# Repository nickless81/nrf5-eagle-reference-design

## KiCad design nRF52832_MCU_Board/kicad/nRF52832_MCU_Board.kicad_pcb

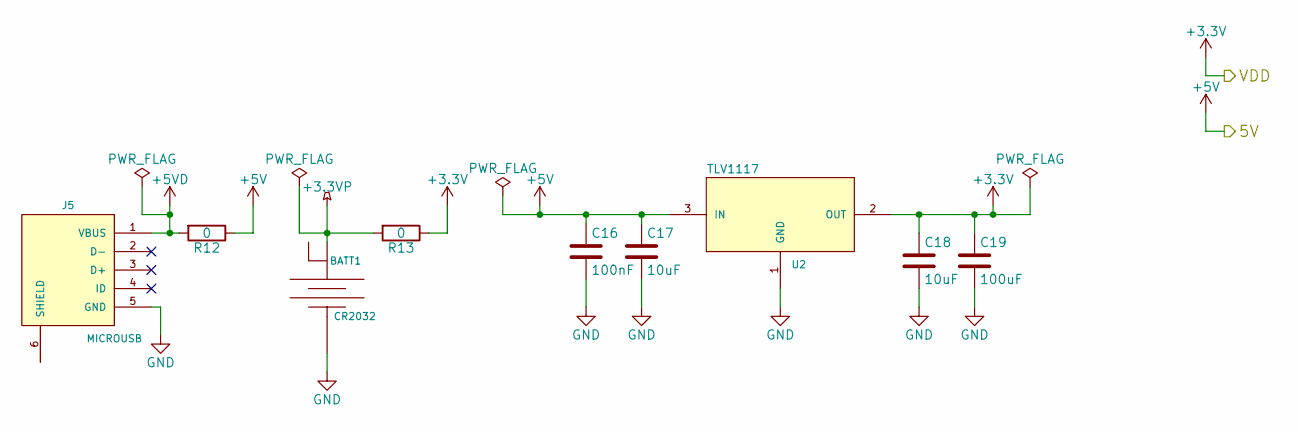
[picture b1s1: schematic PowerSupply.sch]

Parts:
BATT1: CR2032; keystone_3003
C16: 100nF; C_0402
C17, C18: 10uF; C_0603
C19: 100uF; C_0805
J5: MICROUSB; conn_usb_B_micro_smd
R12, R13: 0; R_0402
U2: TLV1117; SOT-223-3Lead_TabPin2

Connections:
+3.3VP: BATT1.2 (+), R13.2
+3V3: C18.1, C19.1, R13.1, U2.2 (OUT); also elsewhere on the board
+5V: C16.1, C17.1, R12.1, U2.3 (IN); also elsewhere on the board
+5VD: J5.1 (VBUS), R12.2
GND: BATT1.1 (-), C16.2, C17.2, C18.2, C19.2, J5.5 (GND), U2.1 (GND); also elsewhere on the board

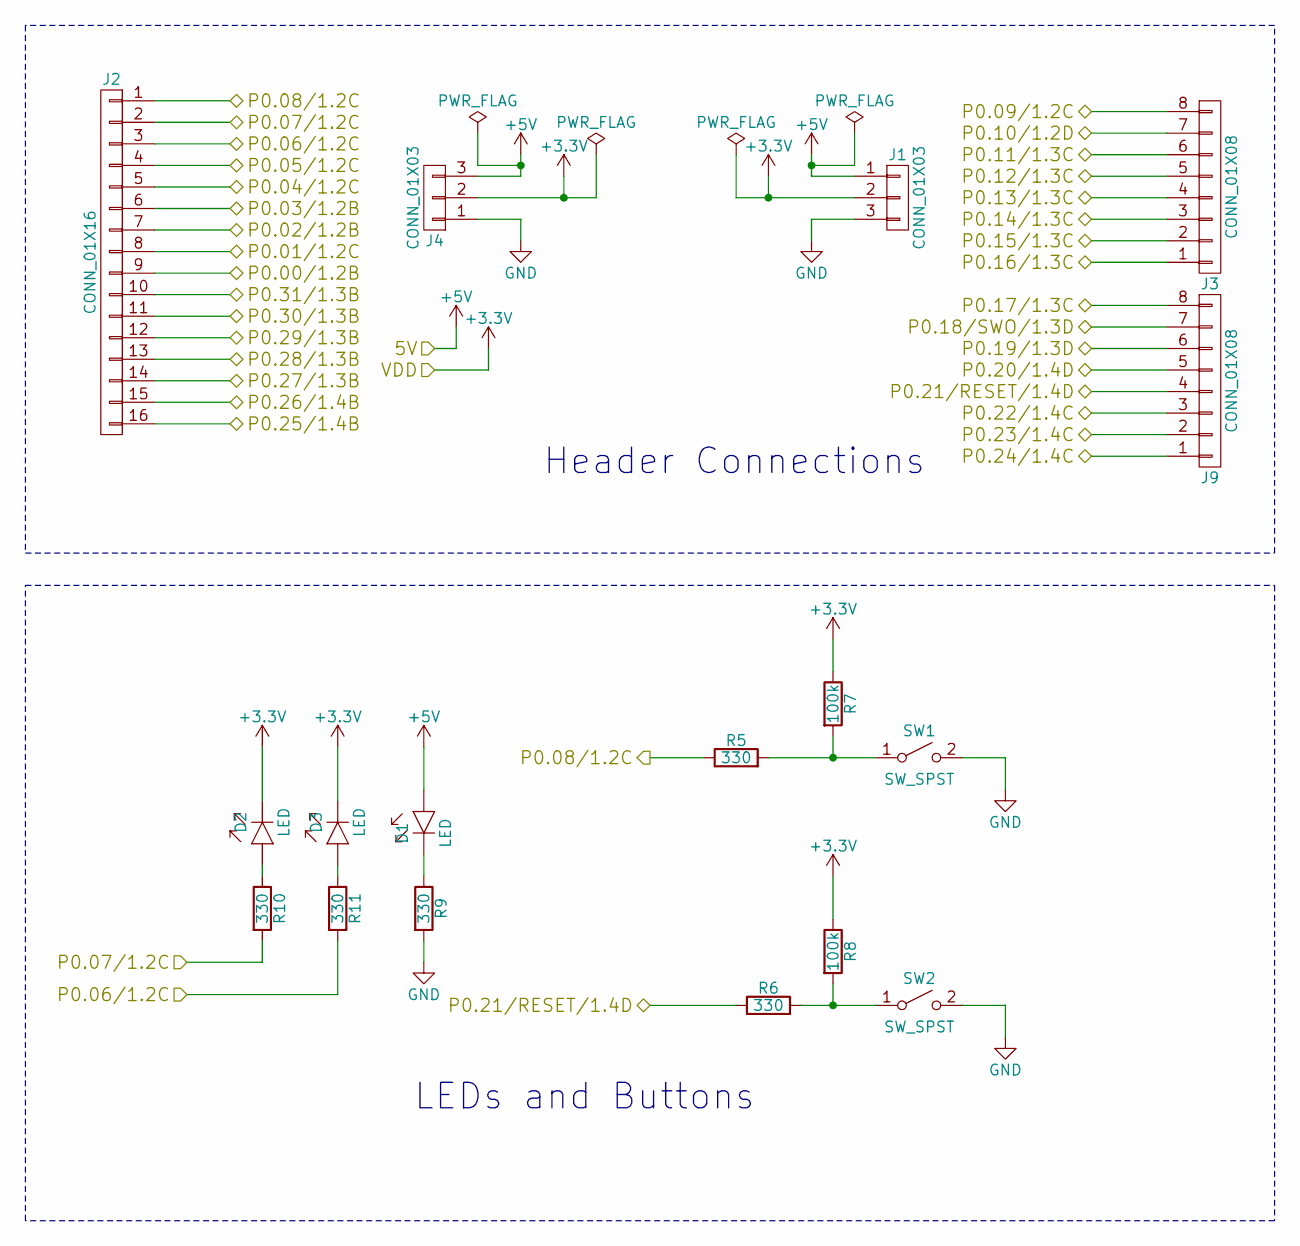
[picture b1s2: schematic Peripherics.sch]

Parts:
D1, D2, D3: LED; LED_0603
J1, J4: CONN_01X03; Pin_Header_Straight_1x03_Pitch2.54mm
J2: CONN_01X16; Pin_Header_Straight_1x16_Pitch2.54mm
J3, J9: CONN_01X08; Pin_Header_Straight_1x08_Pitch2.54mm
R5, R6, R9, R10, R11: 330; R_0402
R7, R8: 100k; R_0402
SW1, SW2: SW_SPST; SW_SPST_FSMSM

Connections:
+3V3: D2.1 (C), D3.1 (C), J1.2, J4.2, R7.1, R8.1; also elsewhere on the board
+5V: D1.2 (A), J1.1, J4.3; also elsewhere on the board
/P0.00: J2.9; also elsewhere on the board
/P0.01: J2.8; also elsewhere on the board
/P0.02: J2.7; also elsewhere on the board
/P0.03: J2.6; also elsewhere on the board
/P0.04: J2.5; also elsewhere on the board
/P0.05: J2.4; also elsewhere on the board
/P0.06: J2.3, R11.2; also elsewhere on the board
/P0.07: J2.2, R10.2; also elsewhere on the board
/P0.08: J2.1, R5.1; also elsewhere on the board
/P0.09: J3.8; also elsewhere on the board
/P0.10: J3.7; also elsewhere on the board
/P0.11: J3.6; also elsewhere on the board
/P0.12: J3.5; also elsewhere on the board
/P0.13: J3.4; also elsewhere on the board
/P0.14: J3.3; also elsewhere on the board
/P0.15: J3.2; also elsewhere on the board
/P0.16: J3.1; also elsewhere on the board
/P0.17: J9.8; also elsewhere on the board
/P0.18: J9.7; also elsewhere on the board
/P0.19: J9.6; also elsewhere on the board
/P0.20: J9.5; also elsewhere on the board
/P0.21: J9.4, R6.1; also elsewhere on the board
/P0.22: J9.3; also elsewhere on the board
/P0.23: J9.2; also elsewhere on the board
/P0.24: J9.1; also elsewhere on the board
/P0.25: J2.16; also elsewhere on the board
/P0.26: J2.15; also elsewhere on the board
/P0.27: J2.14; also elsewhere on the board
/P0.28: J2.13; also elsewhere on the board
/P0.29: J2.12; also elsewhere on the board
/P0.30: J2.11; also elsewhere on the board
/P0.31: J2.10; also elsewhere on the board
GND: J1.3, J4.1, R9.2, SW1.2 (B), SW2.2 (B); also elsewhere on the board
unnamed: D1.1 (C), R9.1
unnamed: D2.2 (A), R10.1
unnamed: D3.2 (A), R11.1
unnamed: R5.2, R7.2, SW1.1 (A)
unnamed: R6.2, R8.2, SW2.1 (A)

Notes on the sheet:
Header Connections
LEDs and Buttons

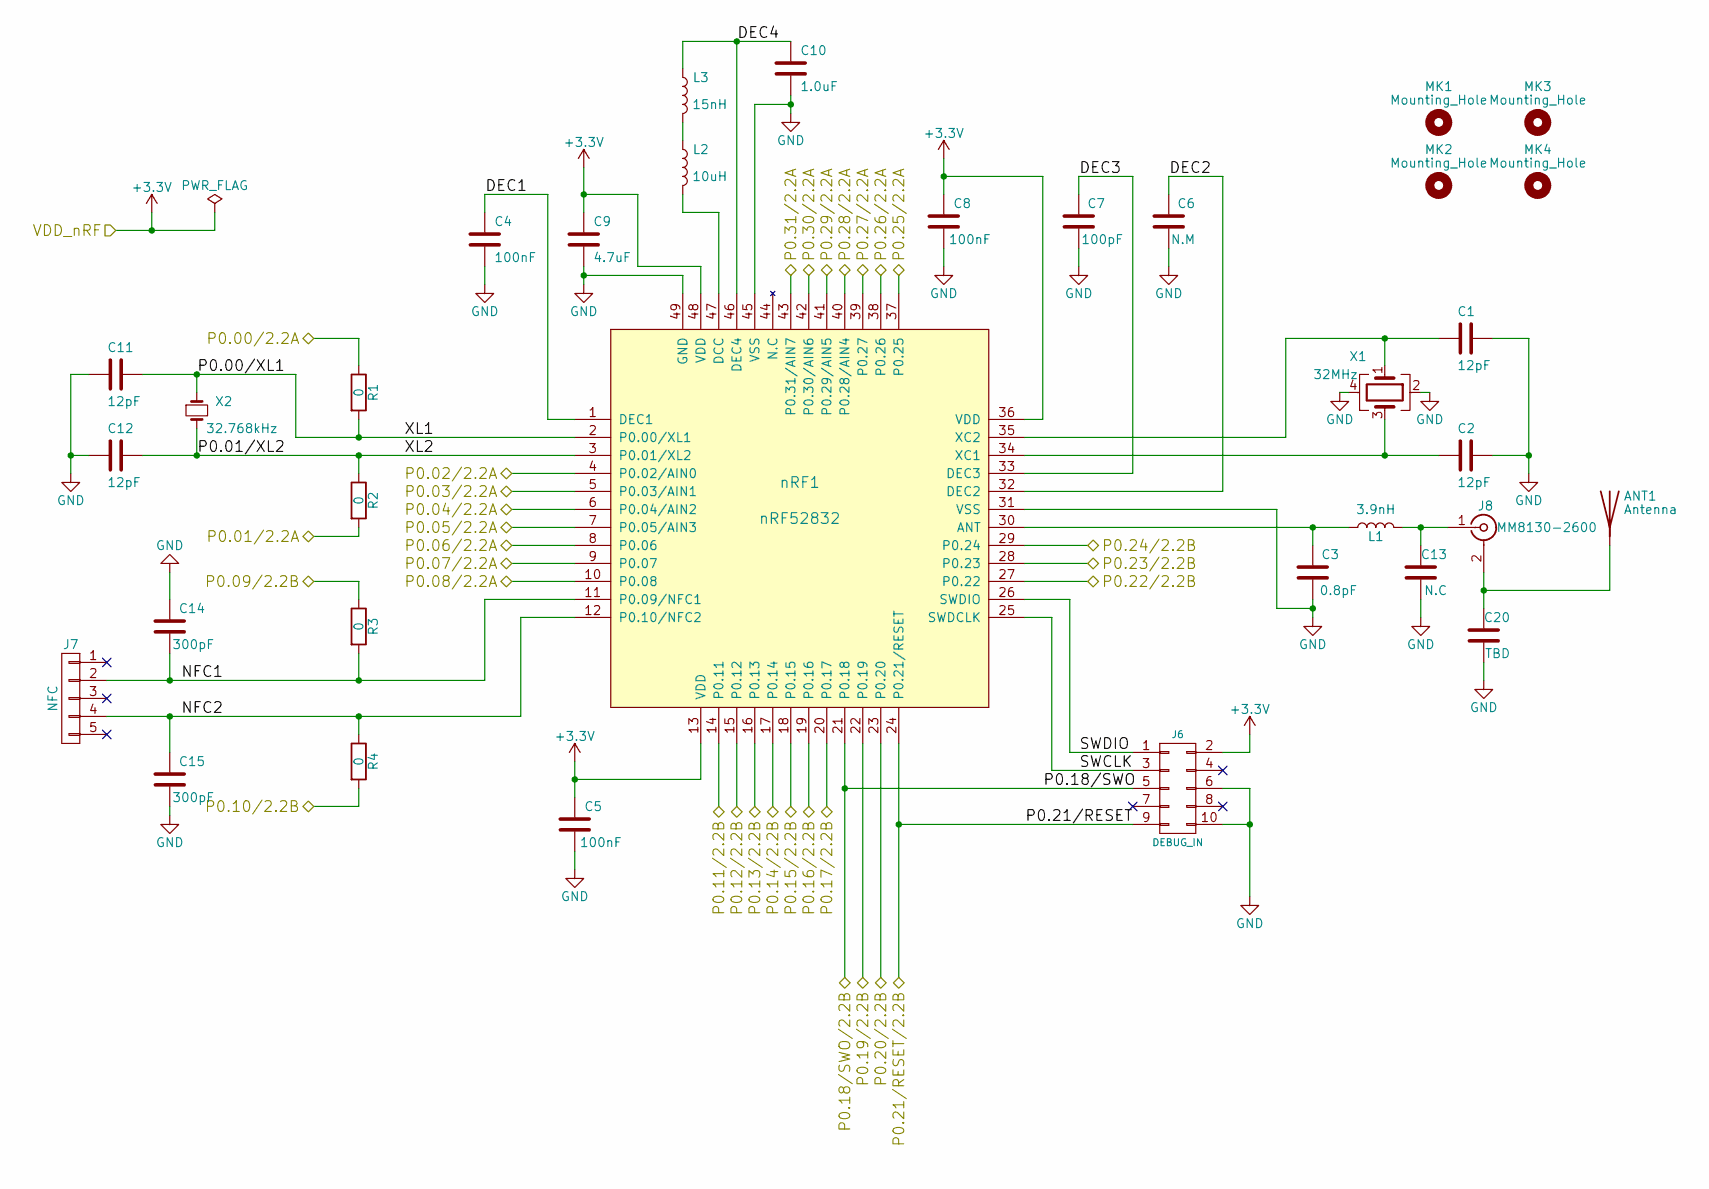
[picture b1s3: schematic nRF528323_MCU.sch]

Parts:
ANT1: Antenna; Nordic_misc-QWMP_MEANDERED_LEFT_+6
C1, C2, C11, C12: 12pF; C_0402
C3: 0.8pF; C_0402
C4, C5, C8: 100nF; C_0402
C6: N.M; C_0402
C7: 100pF; C_0402
C9: 4.7uF; C_0603
C10: 1.0uF; C_0603
C13: N.C; C_0402
C14, C15: 300pF; C_0402
C20: TBD; C_0402
J6: DEBUG_IN; ftsh-105-01-l-dv
J7: NFC; Nordic_misc-FPC_05P-RA-SMD
J8: MM8130-2600; Nordic_misc-MM8130-2600
L1: 3.9nH; L_0402
L2: 10uH; L_0603
L3: 15nH; L_0402
MK1, MK2, MK3, MK4: Mounting_Hole; MountingHole_3mm
R1, R2, R3, R4: 0; R_0402
X1: 32MHz; Crystal_SMD_2016-4pin_2.0x1.6mm
X2: 32.768kHz; Crystal_SMD_3215-2pin_3.2x1.5mm
nRF1: nRF52832; Nordic_nRF-QFN40P600X600X90-48_N

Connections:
+3V3: C5.1, C8.1, C9.1, J6.2, nRF1.13 (VDD), nRF1.36 (VDD), nRF1.48 (VDD); also elsewhere on the board
/P0.00: R1.1; also elsewhere on the board
/P0.01: R2.2; also elsewhere on the board
/P0.02: nRF1.4 (P0.02/AIN0); also elsewhere on the board
/P0.03: nRF1.5 (P0.03/AIN1); also elsewhere on the board
/P0.04: nRF1.6 (P0.04/AIN2); also elsewhere on the board
/P0.05: nRF1.7 (P0.05/AIN3); also elsewhere on the board
/P0.06: nRF1.8 (P0.06); also elsewhere on the board
/P0.07: nRF1.9 (P0.07); also elsewhere on the board
/P0.08: nRF1.10 (P0.08); also elsewhere on the board
/P0.09: R3.1; also elsewhere on the board
/P0.10: R4.2; also elsewhere on the board
/P0.11: nRF1.14 (P0.11); also elsewhere on the board
/P0.12: nRF1.15 (P0.12); also elsewhere on the board
/P0.13: nRF1.16 (P0.13); also elsewhere on the board
/P0.14: nRF1.17 (P0.14); also elsewhere on the board
/P0.15: nRF1.18 (P0.15); also elsewhere on the board
/P0.16: nRF1.19 (P0.16); also elsewhere on the board
/P0.17: nRF1.20 (P0.17); also elsewhere on the board
/P0.18: J6.5, nRF1.21 (P0.18); also elsewhere on the board
/P0.19: nRF1.22 (P0.19); also elsewhere on the board
/P0.20: nRF1.23 (P0.20); also elsewhere on the board
/P0.21: J6.9, nRF1.24 (P0.21/RESET); also elsewhere on the board
/P0.22: nRF1.27 (P0.22); also elsewhere on the board
/P0.23: nRF1.28 (P0.23); also elsewhere on the board
/P0.24: nRF1.29 (P0.24); also elsewhere on the board
/P0.25: nRF1.37 (P0.25); also elsewhere on the board
/P0.26: nRF1.38 (P0.26); also elsewhere on the board
/P0.27: nRF1.39 (P0.27); also elsewhere on the board
/P0.28: nRF1.40 (P0.28/AIN4); also elsewhere on the board
/P0.29: nRF1.41 (P0.29/AIN5); also elsewhere on the board
/P0.30: nRF1.42 (P0.30/AIN6); also elsewhere on the board
/P0.31: nRF1.43 (P0.31/AIN7); also elsewhere on the board
/nRF528323_MCU/DEC1: C4.1, nRF1.1 (DEC1)
/nRF528323_MCU/DEC2: C6.2, nRF1.32 (DEC2)
/nRF528323_MCU/DEC3: C7.2, nRF1.33 (DEC3)
/nRF528323_MCU/DEC4: C10.1, L3.1, nRF1.46 (DEC4)
/nRF528323_MCU/NFC1: C14.2, J7.2, R3.2, nRF1.11 (P0.09/NFC1)
/nRF528323_MCU/NFC2: C15.1, J7.4, R4.1, nRF1.12 (P0.10/NFC2)
/nRF528323_MCU/P0.00/XL1: C11.1, R1.2, X2.1, nRF1.2 (P0.00/XL1)
/nRF528323_MCU/P0.01/XL2: C12.1, R2.1, X2.2, nRF1.3 (P0.01/XL2)
/nRF528323_MCU/SWCLK: J6.3, nRF1.25 (SWDCLK)
/nRF528323_MCU/SWDIO: J6.1, nRF1.26 (SWDIO)
GND: C1.1, C2.1, C3.1, C4.2, C5.2, C6.1, C7.1, C8.2, C9.2, C10.2, C11.2, C12.2, C13.1, C14.1, C15.2, C20.1, J6.6, J6.10, X1.2, X1.4, nRF1.31 (VSS), nRF1.45 (VSS), nRF1.49 (GND); also elsewhere on the board
unnamed: ANT1.1, C20.2, J8.2 (Ext)
unnamed: C1.2, X1.1, nRF1.35 (XC2)
unnamed: C2.2, X1.3, nRF1.34 (XC1)
unnamed: C3.2, L1.1, nRF1.30 (ANT)
unnamed: C13.2, J8.1 (In), L1.2
unnamed: L2.1, L3.2
unnamed: L2.2, nRF1.47 (DCC)

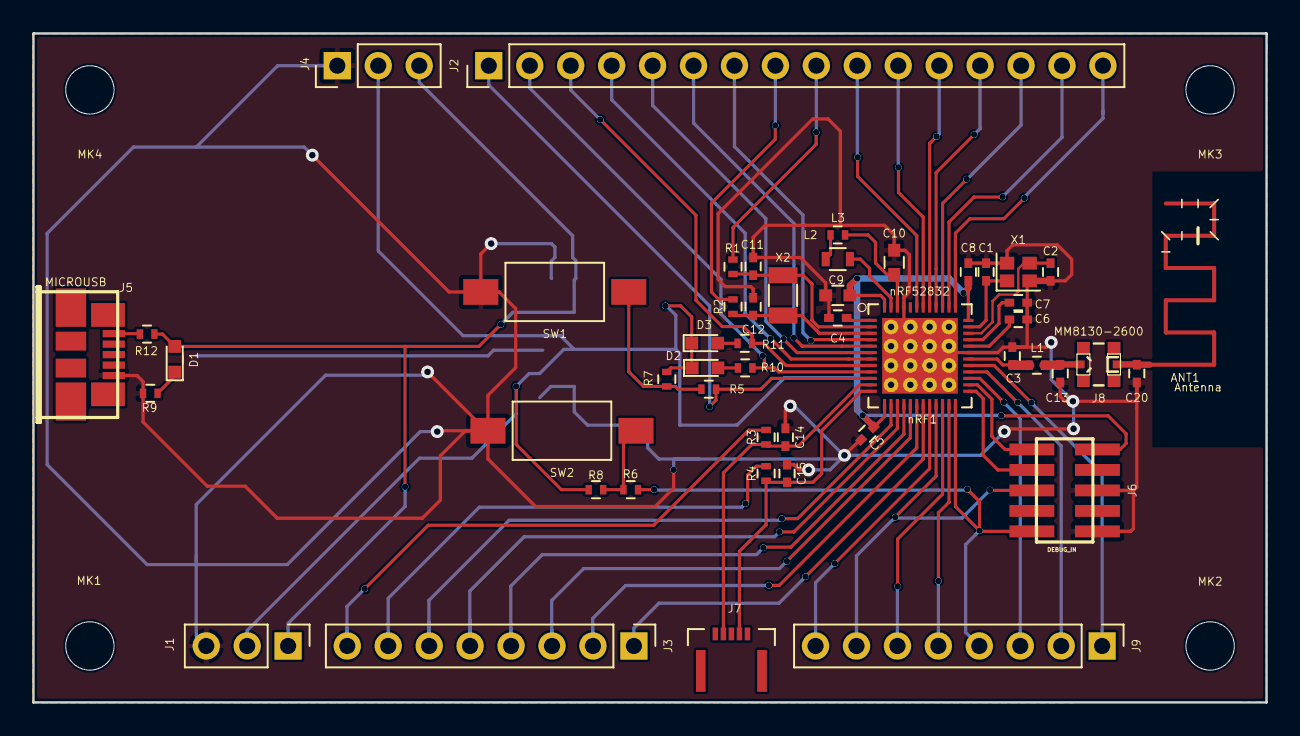
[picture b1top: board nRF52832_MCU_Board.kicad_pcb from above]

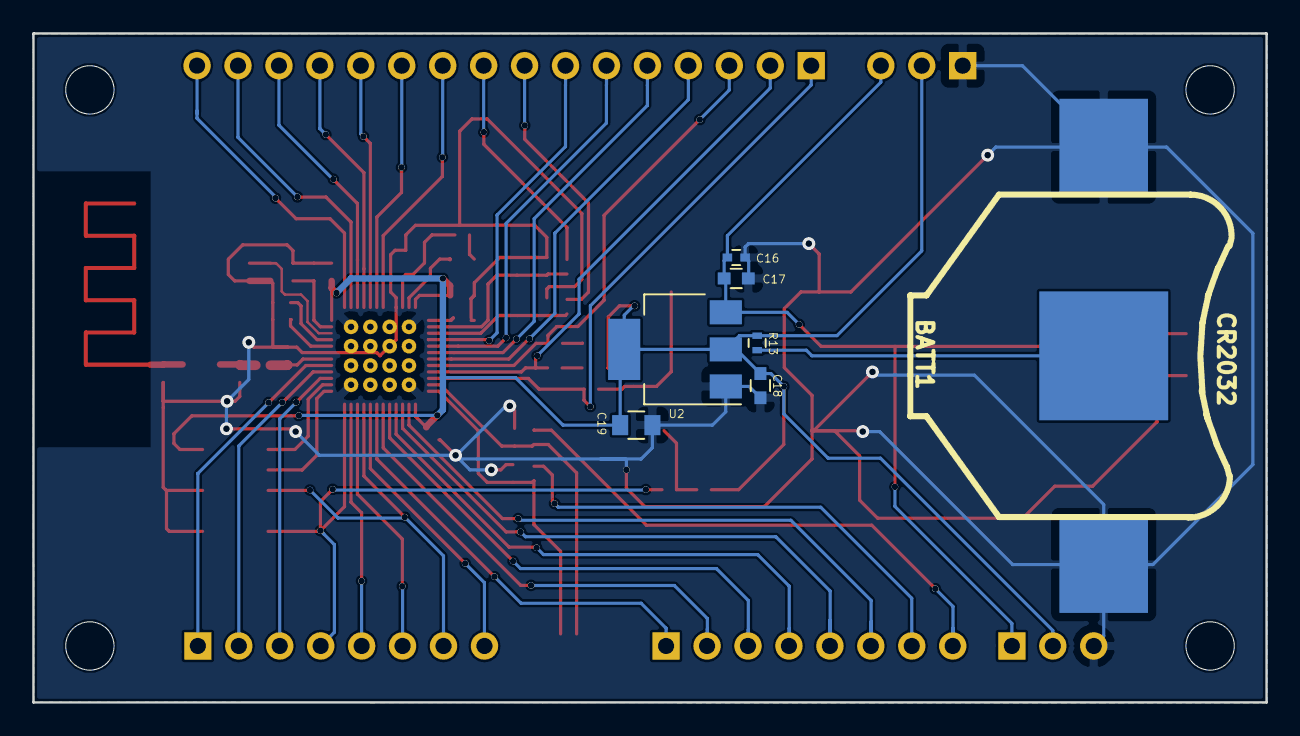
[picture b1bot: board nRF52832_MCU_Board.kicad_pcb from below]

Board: 2 copper layers, 76.5 x 41.5 mm, 60 parts (7 on the bottom side), 59 nets.

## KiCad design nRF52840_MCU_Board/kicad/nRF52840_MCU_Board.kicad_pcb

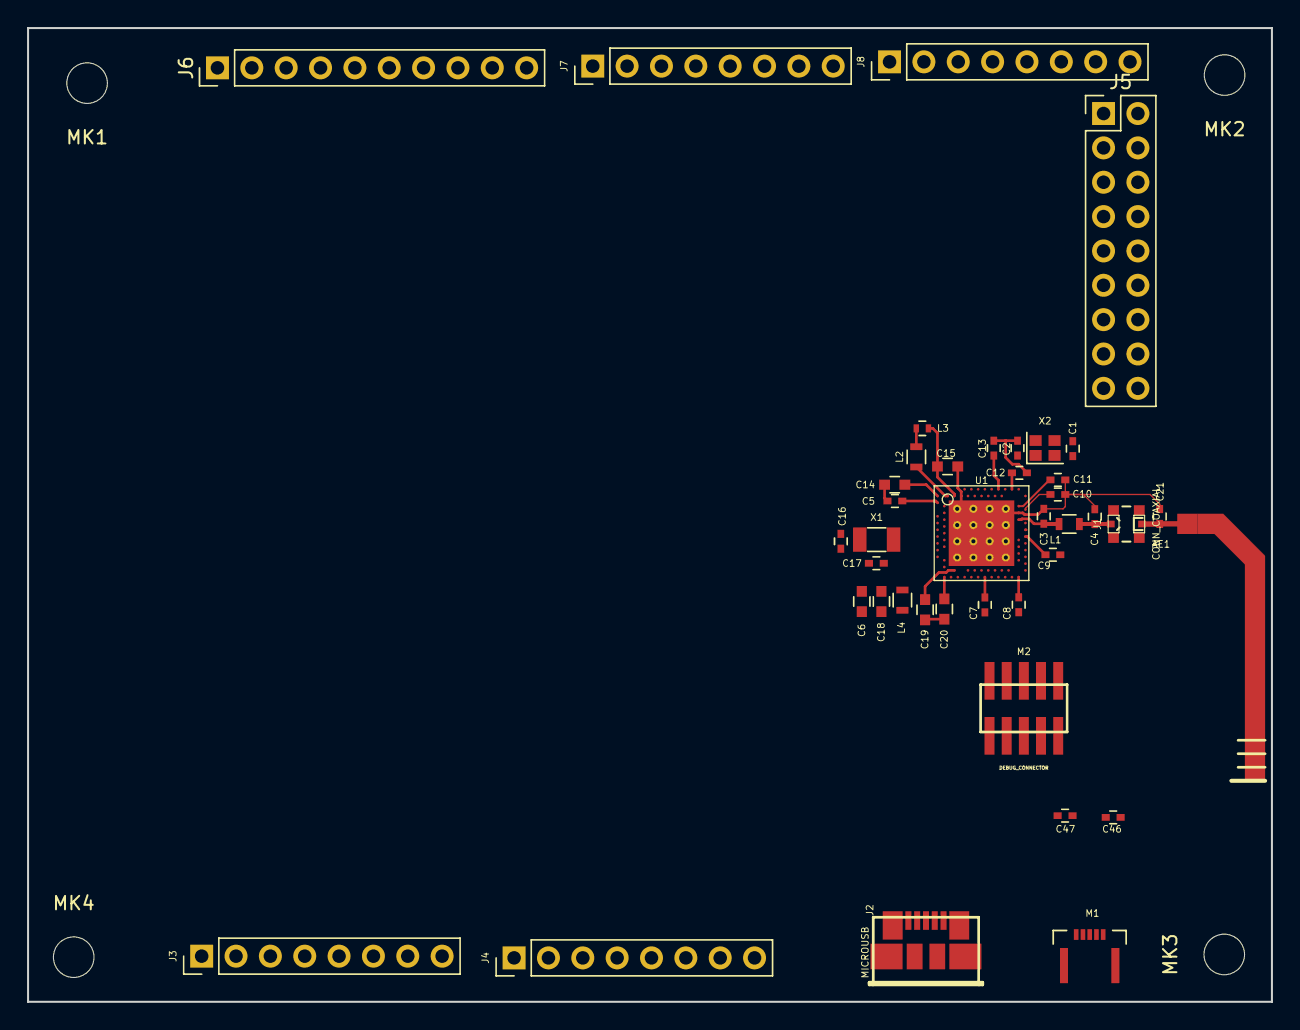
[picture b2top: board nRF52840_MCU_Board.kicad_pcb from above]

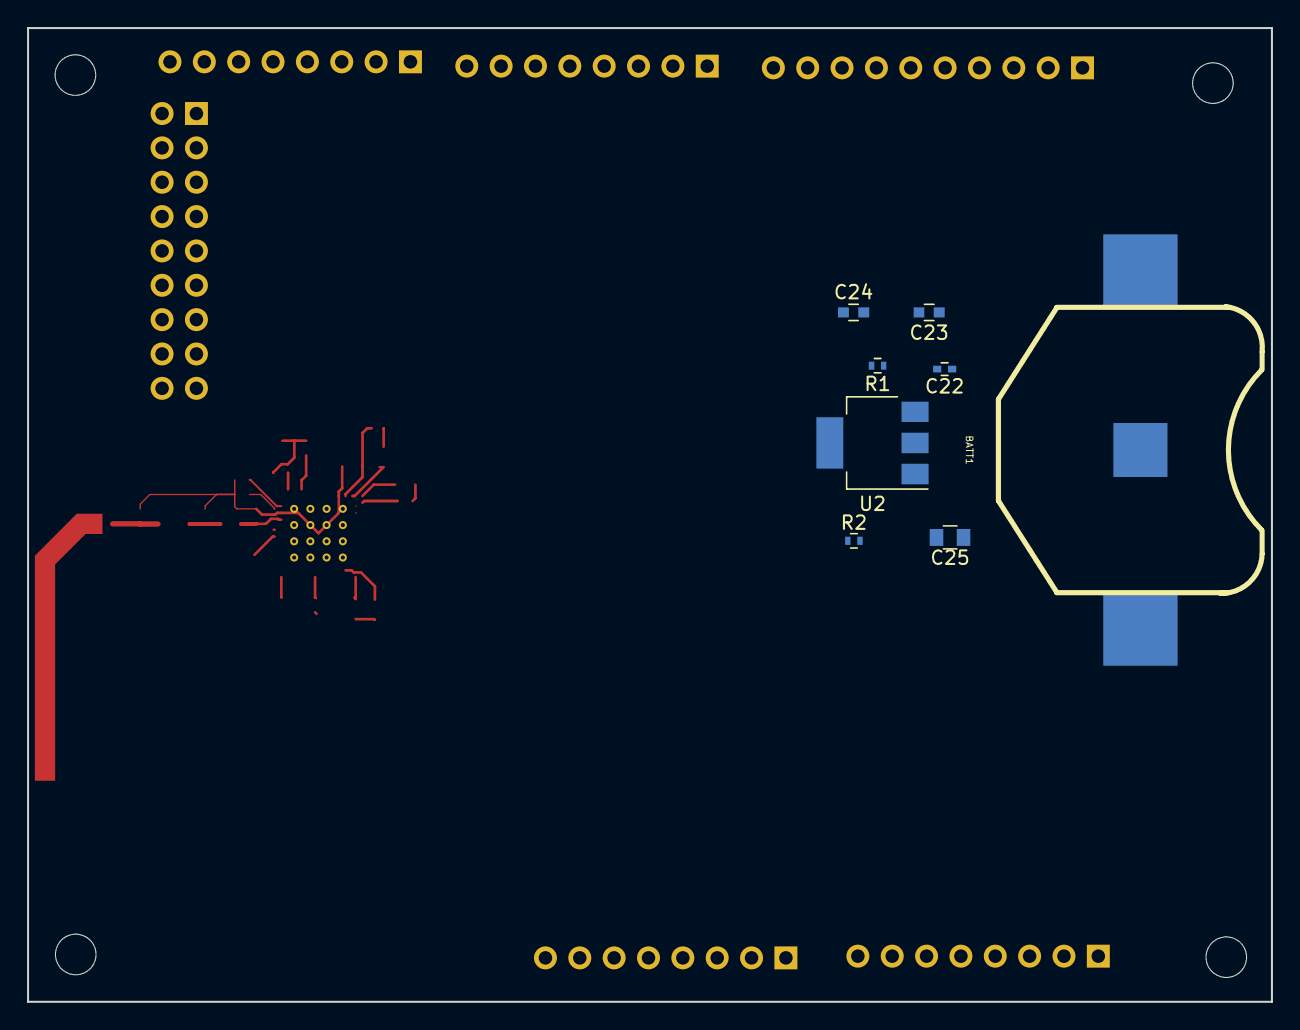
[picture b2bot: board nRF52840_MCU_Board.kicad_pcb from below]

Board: 2 copper layers, 92.0 x 72.0 mm, 53 parts (8 on the bottom side), 33 nets.

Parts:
AE1: Antenna; Nordic_misc-QWMP_BEND_RIGHT_+0
BATT1: CR2032; keystone_3002
C1, C2, C16, C17: 12pF; C_0402
C3: 0.8pF; C_0402
C4: 0.5pF; C_0402
C5, C7, C8, C12, C22: 100nF; C_0402
C6, C18, C19, C20: 4.7uF; C_0603
C9, C10, C13: N.C; C_0402
C11: 100pF; C_0402
C14, C15: 1.0uF; C_0603
C21: 1.2pF; C_0402
C23, C24: 10uF; C_0603
C25: 100uF; C_0805
C46, C47: 300pF; C_0402
J1: CONN_COAXIAL; Nordic_misc-MM8130-2600
J2: MICROUSB; conn_usb_B_micro_smd
J3: Power; Pin_Header_Straight_1x08_Pitch2.54mm
J4: Analog; Pin_Header_Straight_1x08_Pitch2.54mm
J5: Digital3; Pin_Header_Straight_2x09_Pitch2.54mm
J6: Digital0; Pin_Header_Straight_1x10_Pitch2.54mm
J7: Digital1; Pin_Header_Straight_1x08_Pitch2.54mm
J8: Digital2; Pin_Header_Straight_1x08_Pitch2.54mm
L1: 3.3nH; L_0603
L2, L4: 10uH; L_0603
L3: 15nH; L_0402
M1: FPC_05P-RA-SMD; Nordic_misc-FPC_05P-RA-SMD
M2: DEBUG_CONNECTOR; ftsh-105-01-l-dv
MK1, MK2, MK3, MK4: Mounting_Hole; MountingHole_3mm
R1, R2: 0; R_0402
U1: nRF52840; AQFN73_7x7mm
U2: TLV1117; SOT-223-3Lead_TabPin2
X1: XTAL_32KHZ; Crystal_SMD_3215-2pin_3.2x1.5mm
X2: XTAL_32MHZ; Crystal_SMD_2016-4pin_2.0x1.6mm

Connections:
+3.3VP: BATT1.2, R2.2
+3V3: C6.1, C7.1, C8.1, C12.1, C14.1, C20.1, C24.1, C25.1, L4.1, M2.1, R2.1, U1.A22, U1.AD2, U1.AD14, U1.AD23, U1.B1, U1.W1, U2.2
+5V: C22.1, C23.1, R1.1, U2.3
+5VD: J2.1, R1.2
/D+: J2.3, U1.AD6
/D-: J2.2, U1.AD4
/nRF52840/NFC1: C47.2, M1.2, U1.L24
/nRF52840/NFC2: C46.1, M1.4, U1.J24
/nRF52840/P0.18/RESET: M2.10, U1.AC13
/nRF52840/P1.00: M2.6, U1.AD22
GND: BATT1.1, C1.1, C2.1, C3.1, C4.1, C5.2, C6.2, C7.2, C8.2, C9.2, C10.1, C11.1, C12.2, C13.2, C14.2, C15.2, C18.2, C19.2, C20.2, C21.1, C22.2, C23.2, C24.2, C25.2, C46.2, C47.1, J2.5, M2.3, M2.5, M2.9, U1.74, U1.B7, U1.F23, U2.1, X2.2, X2.4
unnamed: C21.2, J1.2
unnamed: C1.2, U1.B24, X2.3
unnamed: C2.2, U1.A23, X2.1
unnamed: C3.2, L1.1, U1.H23
unnamed: C4.2, J1.1, L1.2
unnamed: C5.1, U1.C1
unnamed: C9.1, U1.N24
unnamed: C10.2, U1.E24
unnamed: C11.2, U1.D23
unnamed: C13.1, U1.A18
unnamed: C15.1, L3.1, U1.B5
unnamed: C16.1, U1.D2
unnamed: C16.2, X1.1
unnamed: C17.1, U1.F2
unnamed: C17.2, X1.2
unnamed: C19.1, U1.AC5
unnamed: L2.1, L3.2
unnamed: L2.2, U1.B3
unnamed: L4.2, U1.AB2
unnamed: M2.2, U1.AC24
unnamed: M2.4, U1.AA24
VDD: C18.1, U1.Y2

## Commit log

2017-07-22 Adding *.bak
2017-07-22 Adding initial KiCAD version of nRF52832_qfaa_nfc project
2017-07-22 Adding *.kicad_pcb-bak to git ignore file
2017-07-22 Adding netlist file
2017-07-23 Save work in progress. Working on NFC connector footprint
2017-07-23 Save work in progress before working on RF Antenna
2017-07-24 Update footprint of nRF52840 IC
2017-07-24 Added nrf52840
2017-07-24 Updated bga pad size according to IPC-7351
2017-07-24 Added nRF52810
2017-07-24 Fix libraries' path
2017-07-24 Fix file permission
2017-07-24 Resized Components' Value Label
2017-07-24 reset file permission
2017-07-24 Exporting Modic_misc to KiCad format
2017-07-26 Duplicated Library components removed
2017-07-26 Update module Nordic_misc-pretty
2017-07-26 Library Nordic_nRF exported to Kicad format
2017-07-26 Update KiCad library Nordic_nRF
2017-07-26 Removed duplicated components
2017-07-27 Adding footprint AQFN73_7x7mm
2017-07-27 Update library
2017-07-27 Remove replicated components
2017-07-27 Update KiCAD version of Nordic Libraries (still a WIP)
2017-07-27 Adding footprint 2450AT18B100.kicad_mod and Keystone_3000_1x12mm-CoinCell.kicad_mod
2017-07-28 Update Kicad Library (Adding footprint and 3D model for Screw and Spacer)
2017-07-29 Update Library (KiCAD)
2017-07-29 Reference Project nRF52832_qfaa_nfc ready
2017-07-29 Copy project nRF52832_qfaa_nfc as nRF52832_qfaa_dcdc
2017-07-29 Update Reference Project nRF52832_qfaa_dcdc before open it with KiCad
2017-07-29 Reference Project nRF52832_qfaa_dcdc ready
2017-07-29 Copying Reference Project nRF52832_qfaa_dcdc as nRF52832_qfaa
2017-07-29 Update Reference Project nRF52832_qfaa before open it with KiCad
2017-07-29 Reference Project nRF52832_qfaa ready
2017-07-29 Addinig initial version of Project nRF52832_MCU_Board
2017-07-30 Update footprint
2017-07-30 Update WIP
2017-07-30 Adding 3D models
2017-07-30 Adding footprints
2017-07-30 Adding Schematic file
2017-07-30 Adding more 3D models
2017-07-30 Update KiCad Library (Symbols, Footprint adn 3D Models)
2017-07-30 Update KiCad Projec nRF52832_MCU_Board
2017-07-30 Update 3D models Screw and Spacer 3mm
2017-07-30 Update library Nordic_misc (Mounting Hole)
2017-07-30 Update KiCad Library
2017-07-30 Modified Inductors (To Be Check)
2017-07-30 Update KiCad project nRF52832_MCU_Board
2017-07-31 Update library Nordic_misc and 3D models
2017-07-31 Update FreeCAD 3D model (LED_0603.fcstd)
2017-07-31 Update library (Nordic_misc)
2017-07-31 Adding #D Model UQFN-48-1EP_6x6mm_Pitch0.4mm
2017-07-31 Update KiCAD Library Nordic_nRF (Nordic_nRF-QFN40P600X600X90-48_N)
2017-07-31 Adding 3D models (CR2032-BatteryHolder)
2017-08-01 Adding 3D model
2017-08-01 Update KiCAD footprint (Nordic_nRF.pretty)
2017-08-01 Adding 3D Model SW_SPST_FSMSM
2017-08-01 Update KiCAD library Nordic_misc
2017-08-01 Update KiCAD Project nRF52832_MCU_Board
2017-08-01 Update FreeCAD 3D model
2017-08-03 Adding footprint to libraru Nordic_misc
2017-08-03 Update library Nordic_misc
2017-08-03 Update 3D Model
2017-08-03 Update kicad-_pcb file of project nRF52832_MCU_Board
2017-08-03 Adding nRF52840_reference for KiCAD (initial design)
2017-08-04 Addin footprint (C_402)
2017-08-04 Update KiCAD libraries
2017-08-04 Update KiCAD Project nRF52840_qfaa_nfc
2017-08-04 Adding footprint on library Nordic_misc.pretty
2017-08-04 Update 3D models
2017-08-04 Update .gitignore file
2017-08-04 Copy KiCAD Project nRF52840_qfaa_nfc as nRF52840_qfaa_dcdc
2017-08-04 Update KiCAD project nRF52840_qfaa_dcdc
2017-08-04 Update Library Nordic_nRF
2017-08-04 Copy KiCAD Project nRF52840_qfaa_dcdc as nRF52840_qfaa
2017-08-04 Renamed files
2017-08-04 Update KiCAD Project nRF52840_qfaa
2017-08-04 Copy nRF52840_qfaa_nfc as nRF52840_MCU_Board
2017-08-04 Update KiCAD Project nRF52840_MCU_Board
2017-08-06 Adding #D MOdel Keystone_3002-BatteryHolder
2017-08-06 Adding footprint keystone_3002 on Library Nordic_misc
2017-08-06 Adding 3D Model 1x10-male-pin-header
2017-08-06 Adding 3D Model 2x9-male-pin-header
2017-08-06 Adding 3D Model 1x8-male-pin-header
2017-08-06 Update 3D Models 1x8-male-pin-header and 1x10-male-pin-header
2017-08-09 Adding 3D Model 2450AT43B100-EB1SMA
2017-08-09 Adding 3D Models Molex_SlimStack_Plug_2x11_Pitch0.5mm_55560-0227 and Molex_SlimStack_Plug_2x11_Pitch0.5mm_55560-0307
2017-08-09 Update 3D Model 2450AT43B100-EB1SMA
2017-08-10 Reload footprint
2017-08-10 Addign FreCad file (Initial version)
2017-08-10 Update 3D Model (WIP)
2017-08-10 Update 3D Model and footprint
2017-08-31 Update nRF52832_reference
2017-08-31 Update nRF52840_reference
2017-08-31 Update project nRF52832_MCU_Board
2017-08-31 Update project nRF52840_MCU_Board
2017-08-31 Adding README.md file
2017-08-31 Update README.md file
2017-08-31 Adding README.md files
2017-08-31 Update nRF52832_MCU_Board.png file
2017-08-31 Update minors trace changes
2017-09-05 Update nRF52832_MCU_Board
2018-01-13 Added description
2018-01-13 Fixed description for CIAA_WLCSP_C62_N.pac
2019-06-21 fix(project): change GitHub organization to NordicPlayground
2019-06-21 Mislabeled nRF52840 DEC6 Pin, closes #5
2019-06-21 Started nRF52840 reference layout
2019-06-21 Removed 'nRF52832_MCU-board'
2019-06-21 Resized nRF52810 schematic symbol to same size as nRF52832, also renamed to the proper Packet variant name
2019-06-21 Generated pdfs
2019-06-21 Added nRF52810_qfaa reference layout (copied from nRF52832_qfaa, pin compatible)
2019-06-21 Same fixes as in qfaa_dcdc
2019-06-21 Added nRF52810_qcaa reference
2019-06-21 Small label/designator update, fixes #6
2019-06-21 Added packaging codes in names
2019-06-21 Added clarification that only the Altium reference designs are official
2019-06-21 Updated nRF52840 pad sizes to match altium library
2019-06-21 Eagle did not save properly
